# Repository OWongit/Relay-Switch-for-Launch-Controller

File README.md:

# **Relay Switch Board**

## **Overview**
This is a small relay daughterboard for a rocket launch controller. It lets a low-current 5 V GPIO signal safely switch a fused 5 V power line through an opto-isolated relay, while providing clear power and status indication.

---

## **How It Works**
- **GPIO → Optocoupler**: The GPIO pin drives an optocoupler, isolating the controller from the relay coil circuit.
- **Optocoupler → Transistor**: The optocoupler output drives a transistor that switches current through the relay coil.
- **Protection**: A flyback diode protects the transistor from coil transients.
- **Relay Path**: When energized, the relay connects **RelayIn** to **RelayOut** through a fuse.
- **Indicators**: On-board LEDs show when 5 V is present and when the relay/GPIO is active.

---

## Schematic

## PCB Layout

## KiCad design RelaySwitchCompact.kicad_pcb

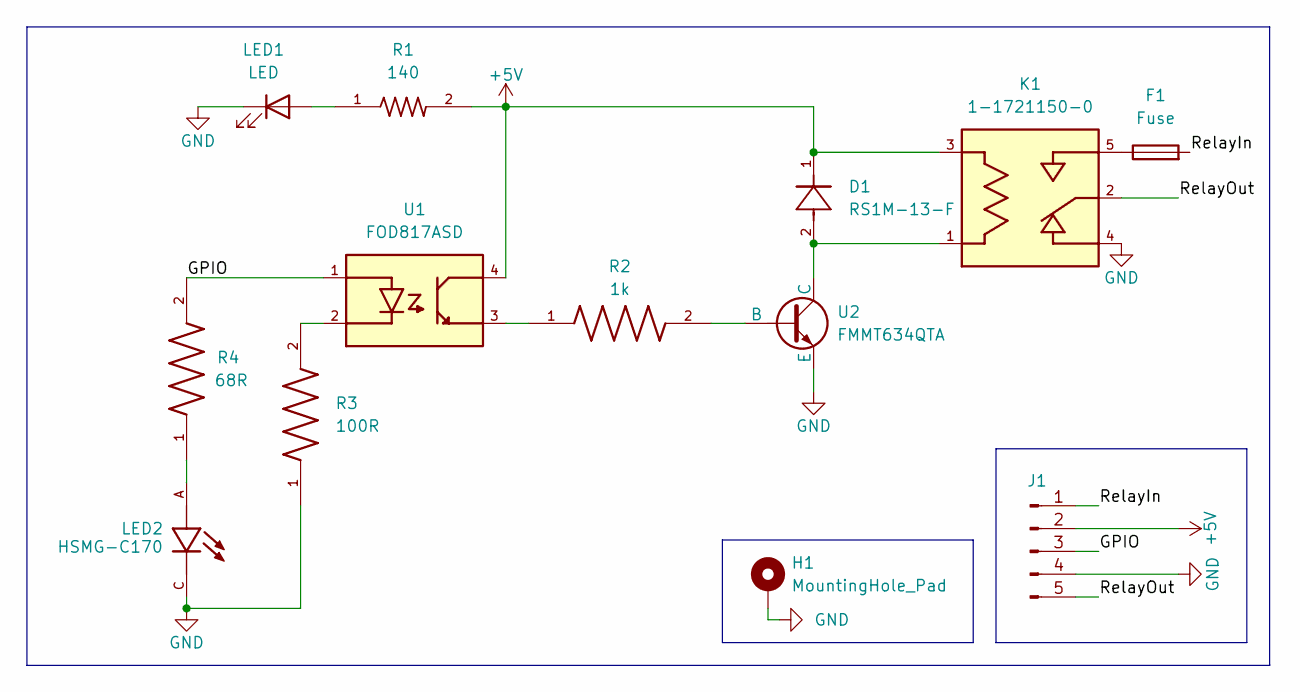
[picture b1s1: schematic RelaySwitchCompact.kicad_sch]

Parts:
D1: RS1M-13-F; SMA_DIO-M; MANUFACTURER_PART_NUMBER RS1M-13-F
F1: Fuse; D_0402_1005Metric_Pad0.77x0.64mm_HandSolder
H1: MountingHole_Pad; MountingHole_3.7mm_Pad
J1: 350-10-105-00-001101; PinHeader_1x05_P2.54mm_Vertical
K1: 1-1721150-0; RELAY_1-1721150-0; PARTREV D
LED1: LED; LED_SML-D12V1WT86
LED2: HSMG-C170; LED_HSMS-C170; PARTREV March 25, 2022
R1: 140; RESC1607X60N
R2: 1k; RESC1608X50N
R3: 100R; RESC1608X55N
R4: 68R; RESC1005X35N
U1: FOD817ASD; SOIC254P1016X385-4N
U2: FMMT634QTA; VREG_XC6206P282MR-G

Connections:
+5V: D1.1, J1.2, K1.3, R1.2, U1.4
/GPIO: J1.3, R4.2, U1.1
/RelayIn: F1.2, J1.1
/RelayOut: J1.5, K1.2
GND: H1.1, J1.4, K1.4, LED1.1 (K), LED2.C, R3.1, U2.3 (E)
unnamed: F1.1, K1.5
unnamed: LED1.2 (A), R1.1
unnamed: LED2.A, R4.1
unnamed: R2.1, U1.3
unnamed: R3.2, U1.2
unnamed: R2.2, U2.2 (B)
unnamed: D1.2, K1.1, U2.1 (C)

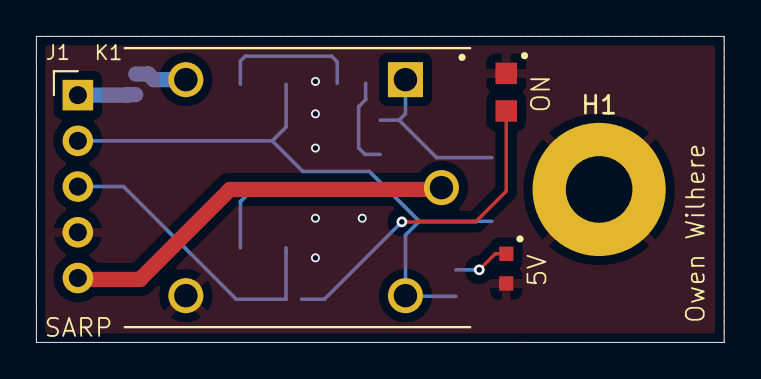
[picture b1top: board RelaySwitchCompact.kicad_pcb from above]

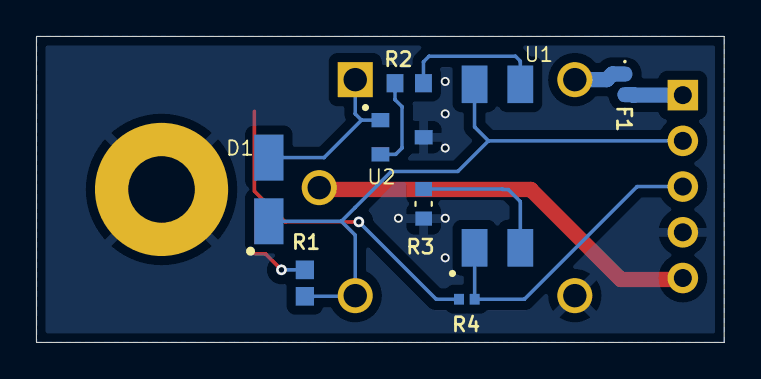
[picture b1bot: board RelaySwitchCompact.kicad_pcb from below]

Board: 2 copper layers, 38.2 x 17.0 mm, 13 parts (8 on the bottom side), 12 nets.

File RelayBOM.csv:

"Reference","Value","Datasheet","Footprint","Qty"
"D1","RS1M-13-F","https://www.diodes.com/assets/Datasheets/ds15002.pdf","RS1M-13-F:SMA_DIO-M","1"
"F1","Fuse","https://industrial.panasonic.com/cdbs/www-data/pdf/AFA0000/A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","Diode_SMD:D_0402_1005Metric_Pad0.77x0.64mm_HandSolder","1"
"J1","350-10-105-00-001101","https://mm.digikey.com/Volume0/opasdata/d220001/medias/docus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","Connector_PinHeader_2.54mm:PinHeader_1x05_P2.54mm_Vertical","1"
"K1","1-1721150-0","https://www.te.com/en/product-1-1721150-0.datasheet.pdf","1-1721150-0:RELAY_1-1721150-0","1"
"LED1","LED","https://fscdn.rohm.com/en/products/databook/datasheet/opto/l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","SML-D12:LED_SML-D12V1WT86","1"
"LED2","HSMG-C170","https://docs.broadcom.com/doc/AV02-0551EN","HSMG-C170:LED_HSMS-C170","1"
"R1","140","https://www.yageo.com/upload/media/product/products/datashee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","RC0603FR-07330RL:RESC1607X60N","1"
"R2","1k","https://www.susumu.co.jp/common/pdf/n_catalog_partition01_en.pdf","RG1608N-102-D-T5:RESC1608X50N","1"
"R3","100R","https://www.yageo.com/upload/media/product/productsearch/dat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","AC0603JR-07100RL:RESC1608X55N","1"
"R4","68R","https://industrial.panasonic.com/cdbs/www-data/pdf/RDA0000/A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","CRCW0402140RFKEDC:RESC1005X35N","1"
"U1","FOD817ASD","https://rocelec.widen.net/view/pdf/yhg4flovvn/ONSM-S-A000316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","FOD817ASD:SOIC254P1016X385-4N","1"
"U2","FMMT634QTA","https://www.diodes.com/assets/Datasheets/FMMT634Q.pdf","FMMT634QTA:VREG_XC6206P282MR-G","1"

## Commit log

2025-01-09 files added
2025-02-20 replaced files
2025-11-04 updated and cleaned up files.
2025-11-04 added images

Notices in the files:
parts and their libraries:
COPYRIGHT: Copyright (C) 2023 Ultra Librarian. All rights reserved.
